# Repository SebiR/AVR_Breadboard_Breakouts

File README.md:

# AVR Breadboard Adapters
Breakout boards for the ATtiny4/5/9/10 and the ATtiny25/45/85V (and others)

## Compatible devices
### SOT23-6
* ATTINY4-TSxR
* ATTINY5-TSxR
* ATTINY9-TSxR
* ATTINY10-TSxR

### SOIC-8 (200mil wide)
* ATtiny11
* ATtiny12

* ATTiny13(V)-[10/20]SU(R)
* ATtiny13A-S[U/H/M/R](R)

ATtiny13A-SU
ATtiny13A-SUR
ATtiny13A-SH
ATtiny13A-SHR
ATtiny13A-SN
ATtiny13A-SNR
ATtiny13A-SF
ATtiny13A-SFR

ATtiny13V-10SU
ATtiny13V-10SUR
ATtiny13-20SU
ATtiny13-20SUR

ATtiny11L-2SC
ATtiny11L-2SI
ATtiny11L-2SU
 ATtiny11-6SC
 ATtiny11-6SI
 ATtiny11-6SU

ATtiny12V-1SC
ATtiny12V-1SI
ATtiny12V-1SU
ATtiny12L-4SC
ATtiny12L-4SI
ATtiny12L-4SU
 ATtiny12-8SC
 ATtiny12-8SI
 ATtiny12-8SU

 84?

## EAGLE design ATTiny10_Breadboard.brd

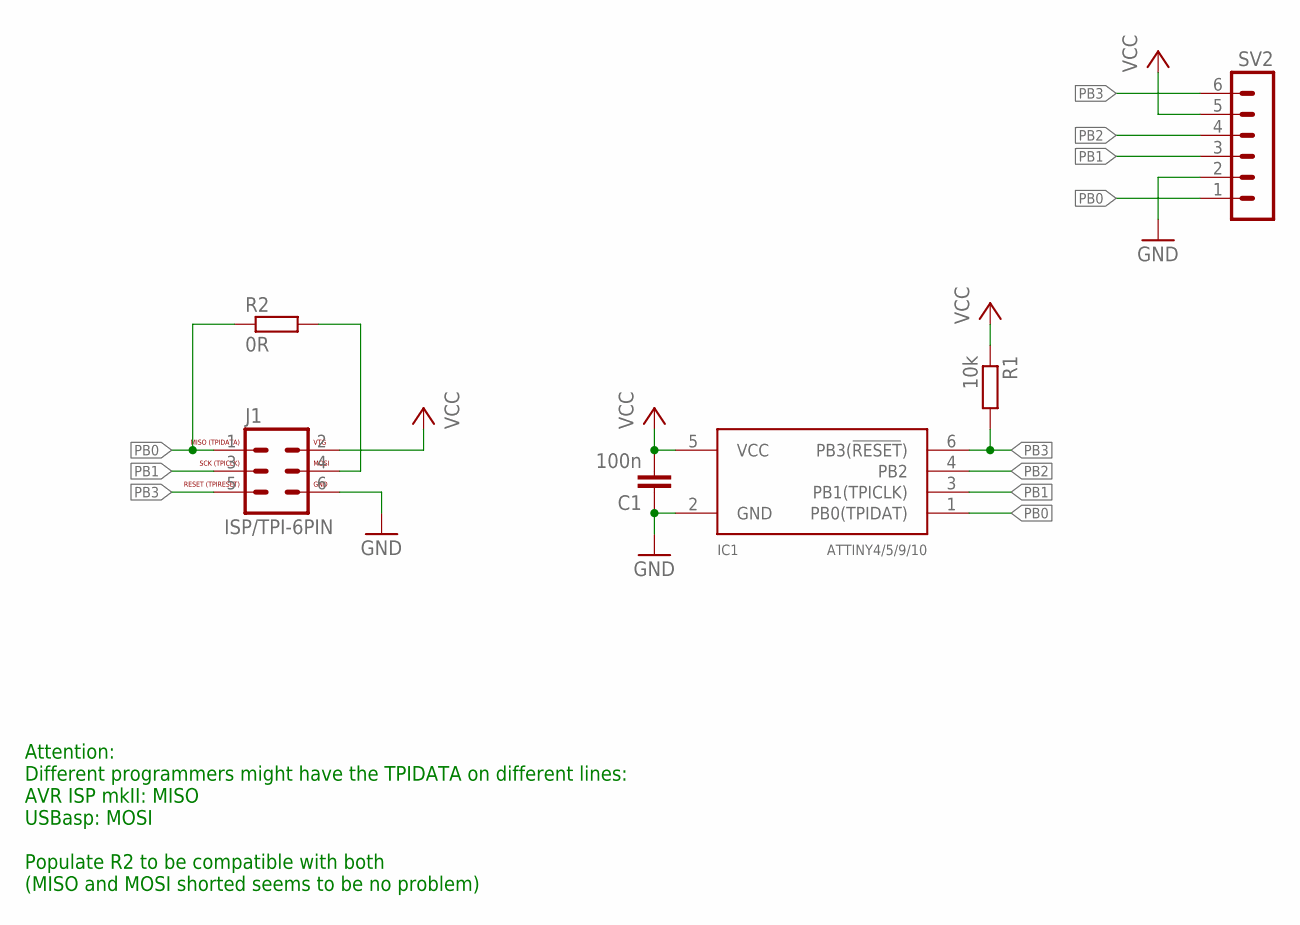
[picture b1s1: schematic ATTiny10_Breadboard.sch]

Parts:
C1: 100n; C0402
IC1: ATTINY4/5/9/10; SOT23-6
J1: ISP/TPI-6PIN; ML6
R1: 10k; R0402
R2: 0R; R0402
SV2: MA06-1

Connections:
GND: C1.1, IC1.2 (GND), J1.6, SV2.2
unnamed: J1.4, R2.2
PB0: IC1.1 (PB0(TPIDAT)), J1.1, R2.1, SV2.1
PB1: IC1.3 (PB1(TPICLK)), J1.3, SV2.3
PB2: IC1.4 (PB2), SV2.4
PB3: IC1.6 (PB3(!RESET!)), J1.5, R1.2, SV2.6
VCC: C1.2, IC1.5 (VCC), J1.2, R1.1, SV2.5

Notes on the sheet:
Attention: Different programmers might have the TPIDATA on different lines: AVR ISP mkII: MISO USBasp: MOSI Populate R2 to be compatible with both (MISO and MOSI shorted seems to be no problem)

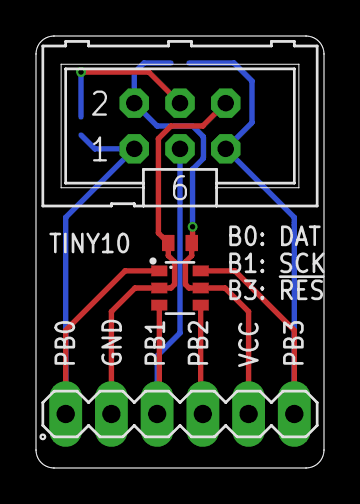
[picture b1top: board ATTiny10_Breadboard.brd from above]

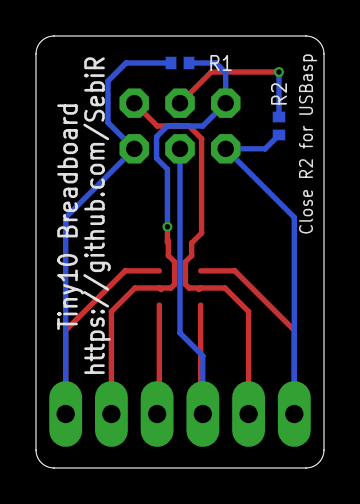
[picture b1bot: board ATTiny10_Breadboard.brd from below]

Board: 2 copper layers, 16.0 x 24.0 mm, 6 parts (2 on the bottom side), 7 nets.

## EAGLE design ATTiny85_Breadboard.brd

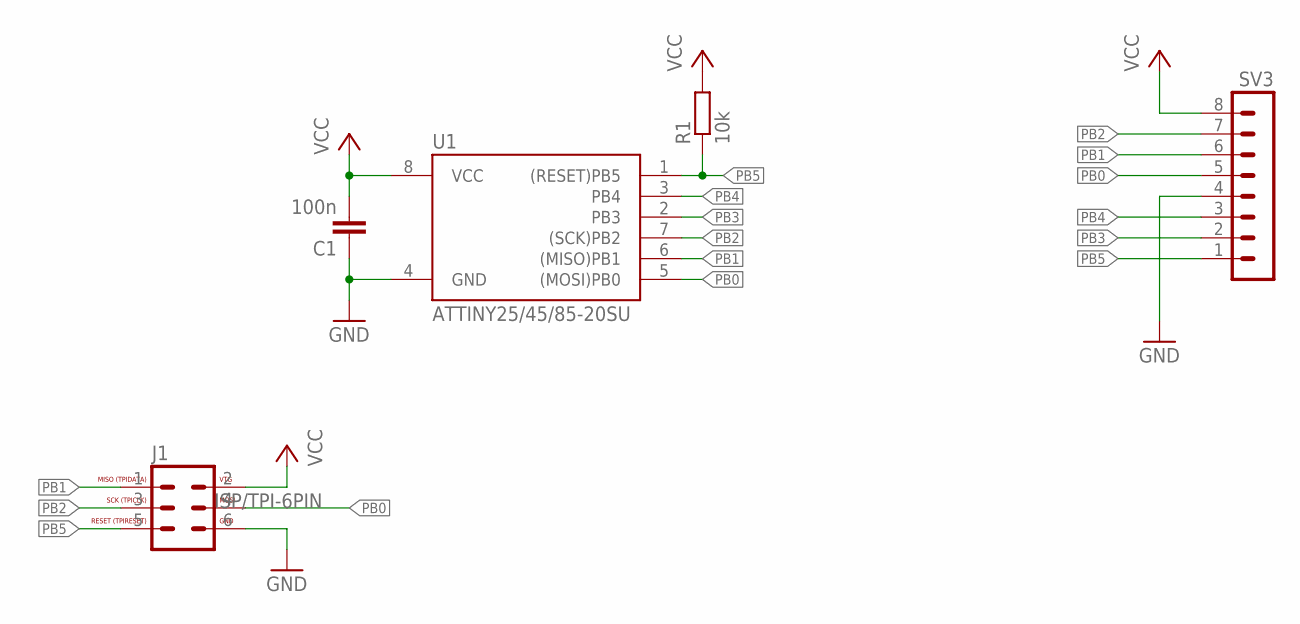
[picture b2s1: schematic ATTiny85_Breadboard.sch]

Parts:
C1: 100n; C0402
J1: ISP/TPI-6PIN; ML6
R1: 10k; R0402
SV3: MA08-1
U1: ATTINY25/45/85-20SU; SOIC8_200

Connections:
GND: C1.1, J1.6, SV3.4, U1.4 (GND)
PB0: J1.4, SV3.5, U1.5 ((MOSI)PB0)
PB1: J1.1, SV3.6, U1.6 ((MISO)PB1)
PB2: J1.3, SV3.7, U1.7 ((SCK)PB2)
PB3: SV3.2, U1.2 (PB3)
PB4: SV3.3, U1.3 (PB4)
PB5: J1.5, R1.1, SV3.1, U1.1 ((RESET)PB5)
VCC: C1.2, J1.2, R1.2, SV3.8, U1.8 (VCC)

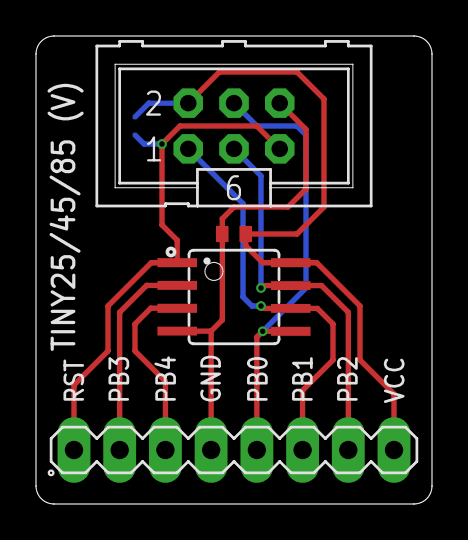
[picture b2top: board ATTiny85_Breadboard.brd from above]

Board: 2 copper layers, 22.0 x 26.0 mm, 5 parts (1 on the bottom side), 8 nets.

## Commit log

2024-12-30 Fixed Tiny10 Board: Now there's an option to connect MISO and MOSI for USBasp compatibility
